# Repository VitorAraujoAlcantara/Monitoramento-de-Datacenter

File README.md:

Monitoramento-de-Datacenter
===========================

Monitoramento de Datacenter

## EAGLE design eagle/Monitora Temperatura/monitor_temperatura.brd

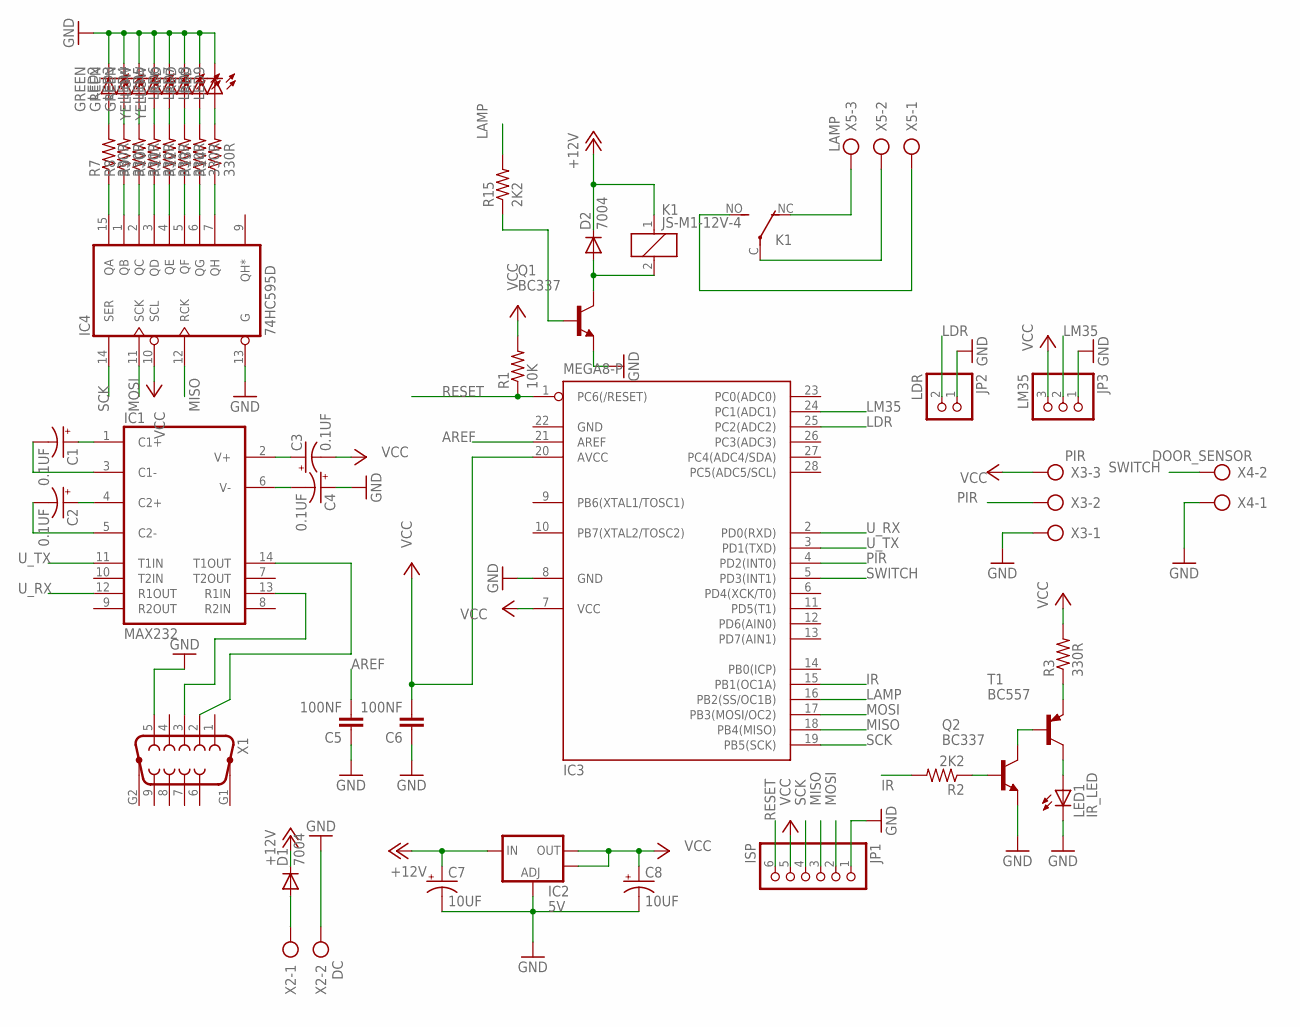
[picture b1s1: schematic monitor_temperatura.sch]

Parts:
C1, C2, C3, C4: 0.1UF; CPOL-RADIAL-10UF-25V
C5, C6: 100NF; CAP-PTH-SMALLEZ
C7, C8: 10UF; CPOL-RADIAL-10UF-25V
D1, D2: 7004; SMA-DIODE_ALT
IC1: MAX232; DIL16
IC2: 5V; SOT223
IC3: MEGA8-P; DIL28-3
IC4: 74HC595D; SO16
JP1: ISP; 1X06
JP2: LDR; 1X02
JP3: LM35; 1X03
K1: JS-M1-12V-4; JS-M
LED1: IR_LED; LED5MM
LED2, LED3, LED4: GREEN; LED5MM
LED5, LED6: YELLOW; LED5MM
LED7, LED8, LED9: RED; LED5MM
Q1, Q2: BC337; TO92
R1: 10K; 0805
R2, R15: 2K2; 0805
R3, R7, R8, R9, R10, R11, R12, R13, R14: 330R; 0805
T1: BC557; TO92
X1: F09HP
X2: DC; AK500/2-H
X3: PIR; AK500/3-H
X4: DOOR_SENSOR; AK500/2-H
X5: LAMP; AK500/3-H

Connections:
+12V: C7.1 (+), D1.C, D2.C, IC2.3 (IN), K1.1
AREF: C5.2, IC3.21 (AREF)
GND: C4.1 (+), C5.1, C6.1, C7.2 (-), C8.2 (-), IC1.15 (GND), IC2.1 (ADJ), IC3.8 (GND), IC3.22 (GND), IC4.8 (GND), IC4.13 (G), JP1.1, JP2.1, JP3.1, LED1.K (C), LED2.K (C), LED3.K (C), LED4.K (C), LED5.K (C), LED6.K (C), LED7.K (C), LED8.K (C), LED9.K (C), Q1.1 (E), Q2.1 (E), X1.5, X2.2, X3.1, X4.1
IR: IC3.15 (PB1(OC1A)), R2.2
LAMP: IC3.16 (PB2(SS/OC1B)), R15.2
LDR: IC3.25 (PC2(ADC2)), JP2.2
LM35: IC3.24 (PC1(ADC1)), JP3.2
MISO: IC3.18 (PB4(MISO)), IC4.12 (RCK), JP1.3
MOSI: IC3.17 (PB3(MOSI/OC2)), IC4.11 (SCK), JP1.2
unnamed: Q2.2 (B), R2.1
unnamed: Q2.3 (C), T1.2 (B)
unnamed: R3.1, T1.1 (E)
unnamed: IC1.14 (T1OUT), X1.2
unnamed: IC1.13 (R1IN), X1.3
unnamed: C1.1 (+), IC1.1 (C1+)
unnamed: C1.2 (-), IC1.3 (C1-)
unnamed: C2.1 (+), IC1.4 (C2+)
unnamed: C2.2 (-), IC1.5 (C2-)
unnamed: C4.2 (-), IC1.6 (V-)
unnamed: C3.1 (+), IC1.2 (V+)
unnamed: D1.A, X2.1
unnamed: IC4.15 (QA), R7.1
unnamed: IC4.1 (QB), R8.1
unnamed: IC4.2 (QC), R9.1
unnamed: IC4.3 (QD), R10.1
unnamed: IC4.4 (QE), R11.1
unnamed: IC4.5 (QF), R12.1
unnamed: IC4.6 (QG), R13.1
unnamed: IC4.7 (QH), R14.1
unnamed: LED2.A, R7.2
unnamed: LED3.A, R8.2
unnamed: LED4.A, R9.2
unnamed: LED5.A, R10.2
unnamed: LED6.A, R11.2
unnamed: LED7.A, R12.2
unnamed: LED8.A, R13.2
unnamed: LED9.A, R14.2
unnamed: LED1.A, T1.3 (C)
unnamed: K1.NC (O), X5.3
unnamed: K1.NO (S), X5.1
unnamed: K1.C, X5.2
unnamed: D2.A, K1.2, Q1.3 (C)
unnamed: Q1.2 (B), R15.1
PIR: IC3.4 (PD2(INT0)), X3.2
RESET: IC3.1 (PC6(/RESET)), JP1.6, R1.1
SCK: IC3.19 (PB5(SCK)), IC4.14 (SER), JP1.4
SWITCH: IC3.5 (PD3(INT1)), X4.2
U_RX: IC1.12 (R1OUT), IC3.2 (PD0(RXD))
U_TX: IC1.11 (T1IN), IC3.3 (PD1(TXD))
VCC: C3.2 (-), C6.2, C8.1 (+), IC1.16 (VCC), IC2.2 (OUT), IC2.4 (OUT), IC3.7 (VCC), IC3.20 (AVCC), IC4.10 (SCL), IC4.16 (VCC), JP1.5, JP3.3, R1.2, R3.2, X3.3

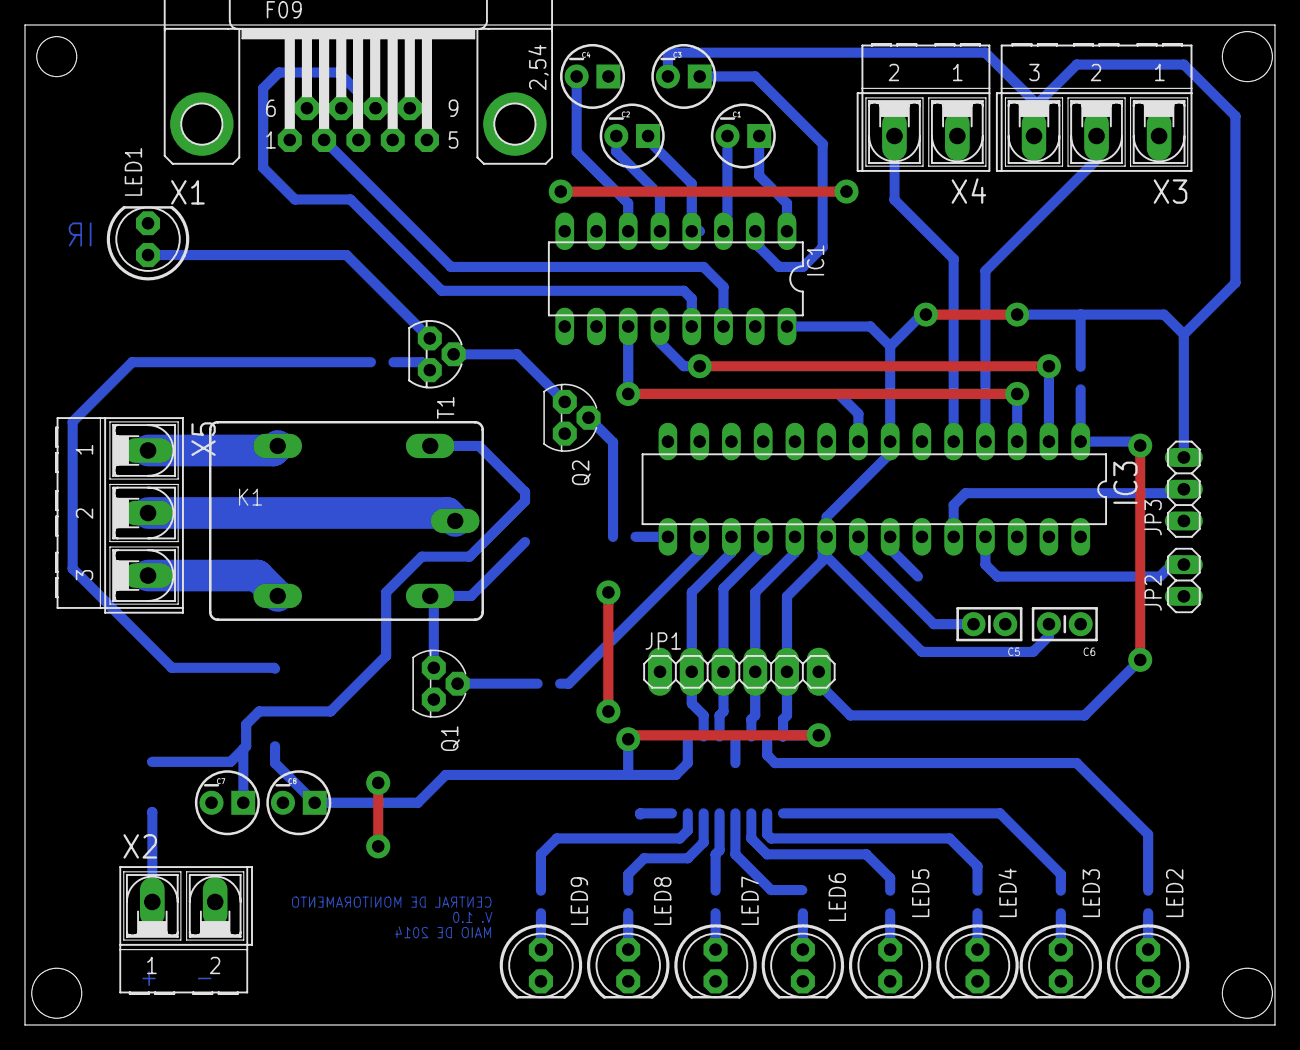
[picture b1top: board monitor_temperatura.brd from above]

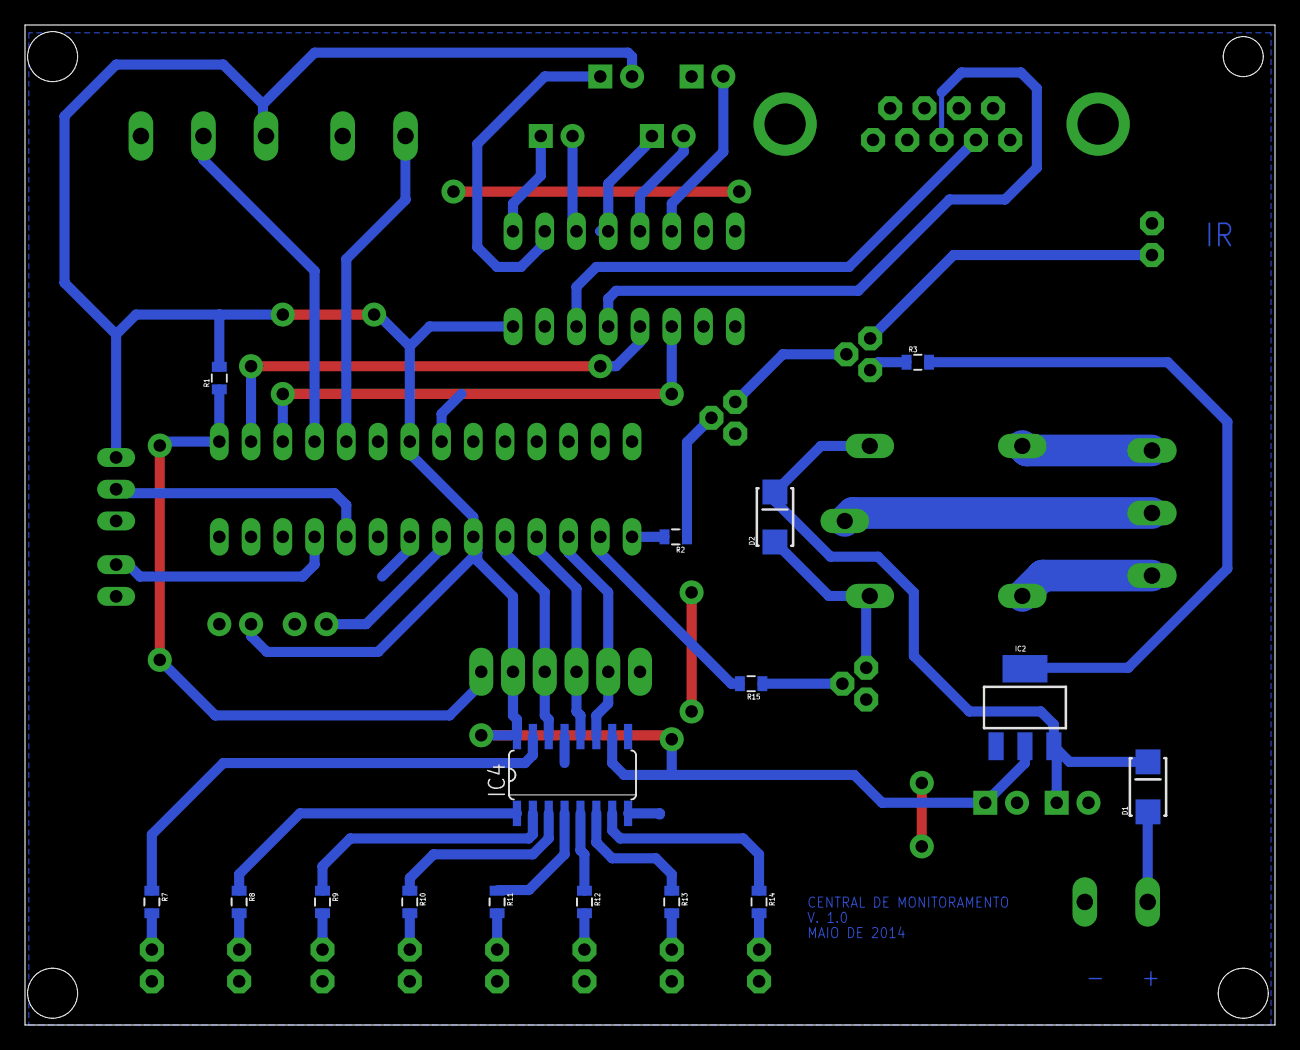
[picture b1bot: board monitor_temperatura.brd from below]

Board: 2 copper layers, 100.0 x 80.0 mm, 47 parts (16 on the bottom side), 50 nets.

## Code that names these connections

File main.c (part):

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// SHIFT
#define HC595_PORT   PORTB
#define HC595_DDR    DDRB
#define HC595_DS_POS PB5      //Data pin (DS) pin location
#define HC595_SH_CP_POS PB3      //Shift Clock (SH_CP) pin location
#define HC595_ST_CP_POS PB4      //Store Clock (ST_CP) pin location
void HC595Init()
{
   //Make the Data(DS), Shift clock (SH_CP), Store Clock (ST_CP) lines output
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   DDRB = 0xff;
   PORTB = 0x00;

   clr_bit(DDRB, PB1); // INFRAVERMELHO

   DDRC = 0xff;
   // CONFIGURANDO LEITURA ANALOGICA TEMPERATURA
   clr_bit(DDRC, PC1);
   PORTC = 0x00;
   clr_bit(DDRC, PC2);

    // CONFIGURANDO ADC
   ADMUX  = 0b11000001;  //Tensão interna de ref (1.1v) canal 0
   ADCSRA = 0b11101110; 

   ADCSRB = 0x00;       // Modo de conversão contínuo
   clr_bit(DIDR0,0);    //desabilita pino PD0 como I/0, entrada do ADC0
   sei();


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{

    // PIR SENSOR
   clr_bit(DDRD, PD2);
   set_bit(PORTD, PD2);

   if ( tst_bit(PIND, PD2) ) {
      escreve_USART("0001 p");
   }
   else
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}

void activeLamp(){
   set_bit(DDRB, PB2);
   set_bit(PORTB, PB2);
   escreve_USART("Liga lampada");
   USART_Transmite('\r');
   USART_Transmite('\n');
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}

void desactiveLamp(){
   set_bit(DDRB, PB2);
   clr_bit(PORTB, PB2);
   escreve_USART("Desliga lampada");
   USART_Transmite('\r');
   USART_Transmite('\n');
}

void showLamp(){
   if ( tst_bit(PORTB, PB2) ){
       escreve_USART("0001 x");
   }
   else
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void ligaPwm()
{
  //DDRB =  0b00000010;
  set_bit(DDRB, PB1);
  //PORTD = 0b10011111;
   //PORTD = 0b10011111;
  // set_bit(TCCR0A, COM0A0);
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
void desligaPwm()
{
   clr_bit(DDRB, PB1);
  //DDRB =  0b00000000;
  //PORTD = 0b00000000;
}
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
void showPortSensor()
{
   clr_bit(DDRD, PD3);
   set_bit(PORTD, PD3);
   if ( tst_bit(PIND, PD3)   ){
      escreve_USART("0000 s");
   }
   else
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
void showLuminosidade()
{
    set_bit(PORTC, PC2);
    _delay_ms(10);
    ADMUX  = 0b11000010;  //Tensão interna de ref (1.1v) 
    _delay_ms(50);
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   USART_Transmite('\n');

    ADMUX  = 0b11000001;  //Tensão interna de ref (1.1v) canal 1
    clr_bit(PORTC, PC2);
    comando = ' ';
}

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
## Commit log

2014-05-05 Inicio do projeto
2014-05-18 ATUALIZAÇÃO
2014-05-18 Inclusão de projeto eagle.
2014-05-18 Adição de atualização em tempo real dos gráficos na camada de visualização.
2014-05-18 Lazarus Inclusão de pacote contendo componente para comunicação serial.
2014-05-19 Comentários.
2014-05-20 Ajuste para exibicao dos graficos em tempo real
2014-05-21 Adicionado imagem para lampada e detecao de presenca.

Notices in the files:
parts and their libraries:
SparkFun-PowerIC: Licensing: Creative Commons ShareAlike 4.0 International - https://creativecommons.org/licenses/by-sa/4.0
